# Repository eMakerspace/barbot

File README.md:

View this project on [CADLAB.io](https://cadlab.io/project/29307). 

# eMakerspace-BarBot

Design your own drinks...
- Use a WordPress configurator to design a drink
- Pay the drink with Twint
- Grab the data with a python script over the WooCommerce API
- Control the robot via the RPi HAT and make the drinks

## Web UI

## RPi HAT

## Processing an order
```
━━━━━━━┳━━━━━━━━━━━━━━━━━━━━━━━━━━━━━━━┳━━━━━━━━━━━━━━
   444 ┃ Marco                         ┃ processing
━━━━━━━╋━━━━━━━━━━━━┳━━━━━━━━━━━━━━━━━━╋━━━━━━━━━━━━━━
    ID ┃ Name       ┃ Filler           ┃ Alc
───────╂────────────╂──────────────────╂──────────────
     0 ┃ Vodka-O    ┃ Orangensaft      ┃ Vodka
     1 ┃ DIY drink  ┃ Citro            ┃ Tequila

Process order 444
Process drink  0/1: Vodka-O
Robot: Waiting for a new cup
Robot: Start movement
Robot: Pouring filler: Orangensaft
Robot: Pouring alcohol: Vodka
Robot: Completed Vodka-O
Process drink  1/1: DIY drink
Robot: Waiting for a new cup
Robot: Start movement
Robot: Pouring filler: Citro
Robot: Pouring alcohol: Tequila
Robot: Completed DIY drink
Completed order 444, upload new status to WordPress
Upload completed
```

### Limitations
No umlauts allowed in the drinks

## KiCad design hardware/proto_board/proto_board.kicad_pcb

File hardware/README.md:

# Modular Hardware

- Nothing is fixed; it will change anyway...
- Make a solid base for creative hacking
- Everything based on ribbon cable
- No free flying hardware and sketchy cables
- Every cable is keyed, no wrong polarities.

| &nbsp;                                    | &nbsp;                                          |
| ----------------------------------------- | ----------------------------------------------- |
|        |        |
|  |  |

## Underling Architecture

- Different boards e.g.
    - IO
    - DC Motors with H-Bridge
    - Stepper motors
    - Proto board
    - Raspberry Pi
    - Main ESP

## BarBot HAT

First try with a fixed version, failed at the first adaption... ;-)

- Raspberry Pi HAT
- SEED Studio ESP32-C3
- One stepper motor driver
- Five 12V outputs, with a Tiny 1.5 A MOSFET Gate Driver
- Neopixel output

| &nbsp;                              | &nbsp;                                    |
| ----------------------------------- | ----------------------------------------- |
|        |        |
|  |  |

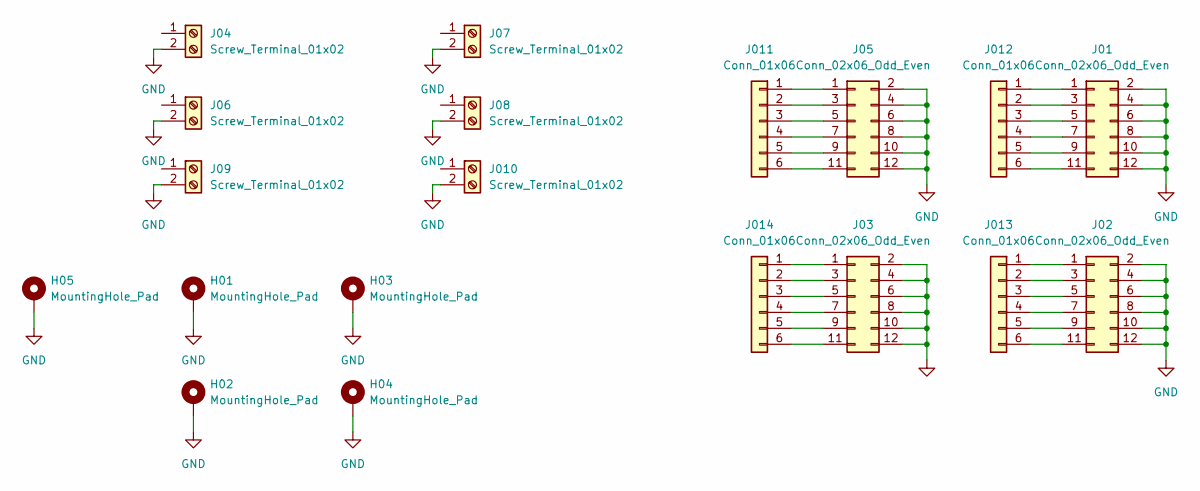
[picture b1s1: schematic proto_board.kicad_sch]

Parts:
H01, H02, H03, H04, H05: MountingHole_Pad; MountingHole_3.2mm_M3_Pad_Via
J01, J02, J03, J05: Conn_02x06_Odd_Even; PinSocket_2x06_P2.54mm_Vertical
J04, J06, J07, J08, J09, J010: Screw_Terminal_01x02; TerminalBlock_MetzConnect_Type055_RT01502HDWU_1x02_P5.00mm_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
J011, J012, J013, J014: Conn_01x06; 6Pin

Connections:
GND: H01.1 (1_1), H02.1 (1_1), H03.1 (1_1), H04.1 (1_1), H05.1 (1_1), J01.2, J01.4, J01.6, J01.8, J01.10, J01.12, J02.2, J02.4, J02.6, J02.8, J02.10, J02.12, J03.2, J03.4, J03.6, J03.8, J03.10, J03.12, J04.2 (Pin_2_2), J05.2, J05.4, J05.6, J05.8, J05.10, J05.12, J06.2 (Pin_2_2), J07.2 (Pin_2_2), J08.2 (Pin_2_2), J09.2 (Pin_2_2), J010.2 (Pin_2_2)
unnamed: J01.1, J012.1
unnamed: J01.3, J012.2
unnamed: J01.5, J012.3
unnamed: J01.7, J012.4
unnamed: J01.9, J012.5
unnamed: J01.11, J012.6
unnamed: J05.1, J011.1
unnamed: J05.3, J011.2
unnamed: J05.5, J011.3
unnamed: J05.7, J011.4
unnamed: J05.9, J011.5
unnamed: J05.11, J011.6
unnamed: J02.1, J013.1
unnamed: J02.3, J013.2
unnamed: J02.5, J013.3
unnamed: J02.7, J013.4
unnamed: J02.9, J013.5
unnamed: J02.11, J013.6
unnamed: J03.1, J014.1
unnamed: J03.3, J014.2
unnamed: J03.5, J014.3
unnamed: J03.7, J014.4
unnamed: J03.9, J014.5
unnamed: J03.11, J014.6

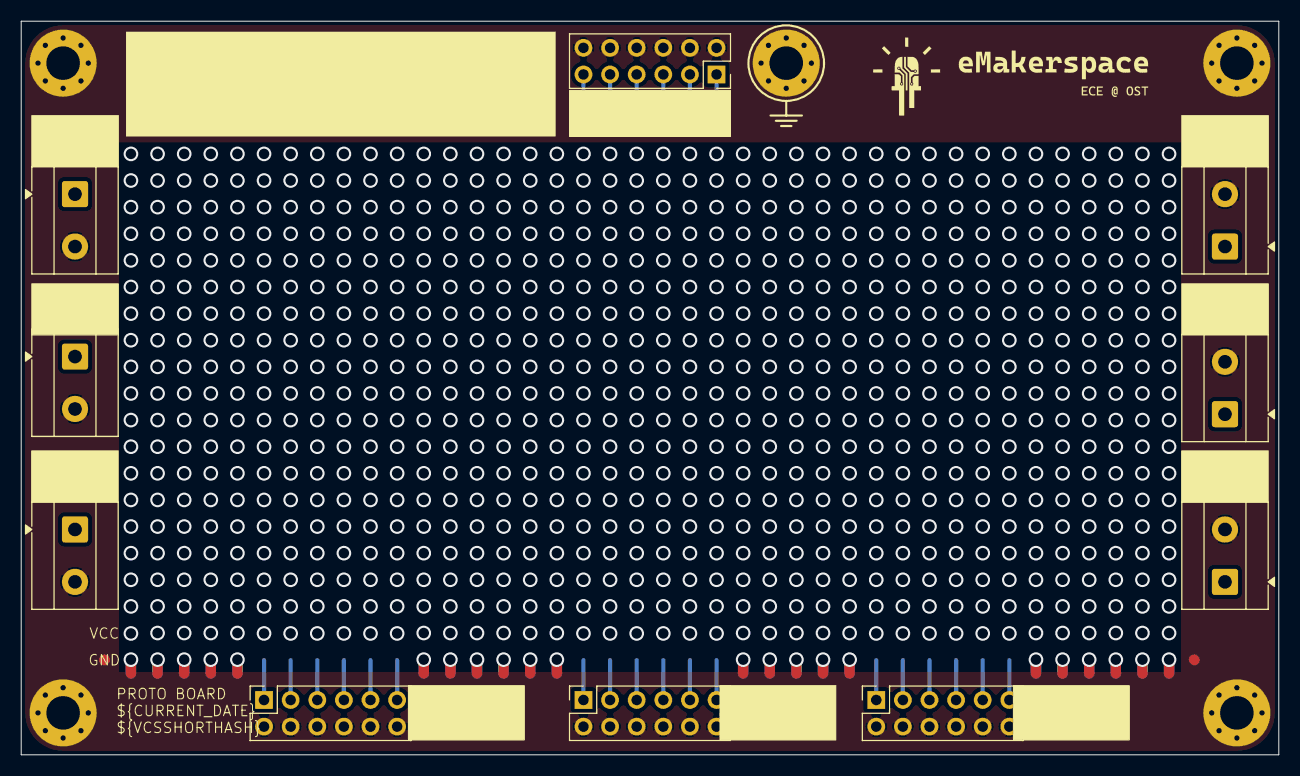
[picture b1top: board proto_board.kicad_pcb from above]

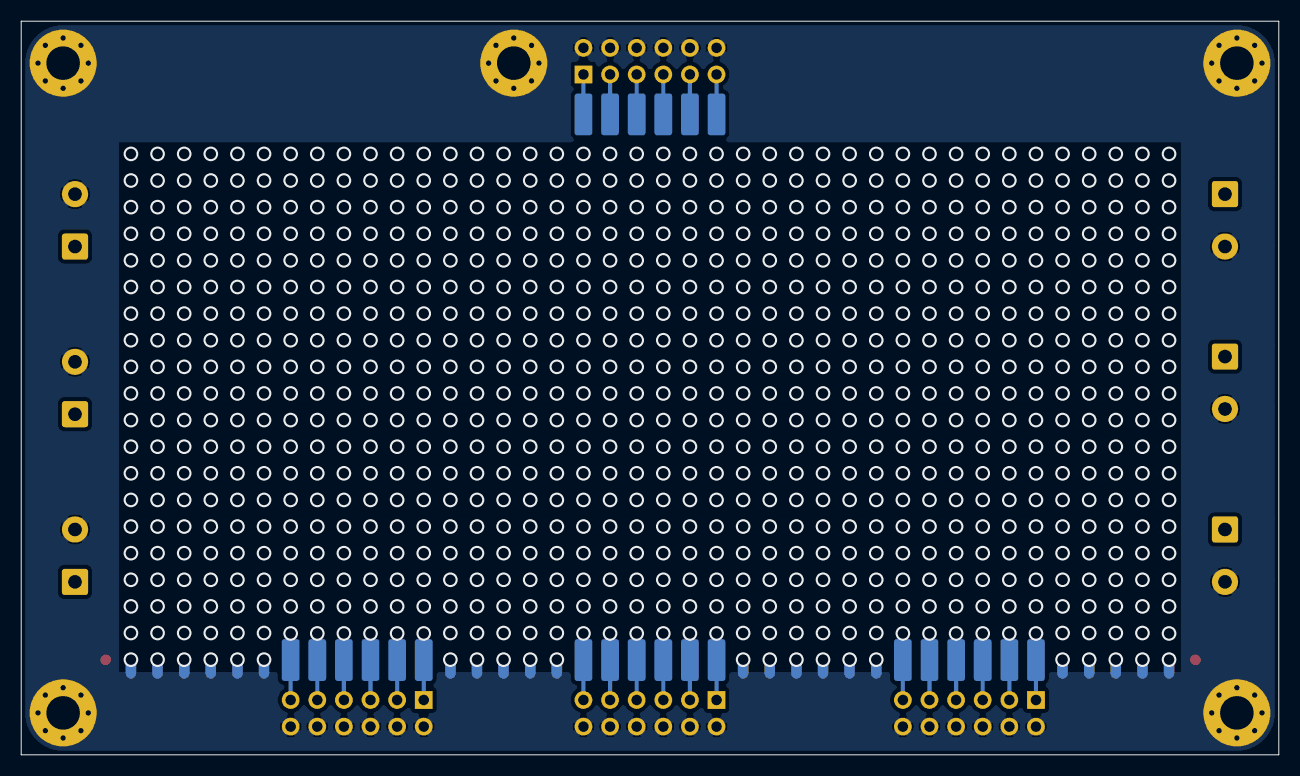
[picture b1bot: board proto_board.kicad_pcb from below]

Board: 2 copper layers, 120.0 x 70.0 mm, 19 parts (4 on the bottom side), 25 nets.

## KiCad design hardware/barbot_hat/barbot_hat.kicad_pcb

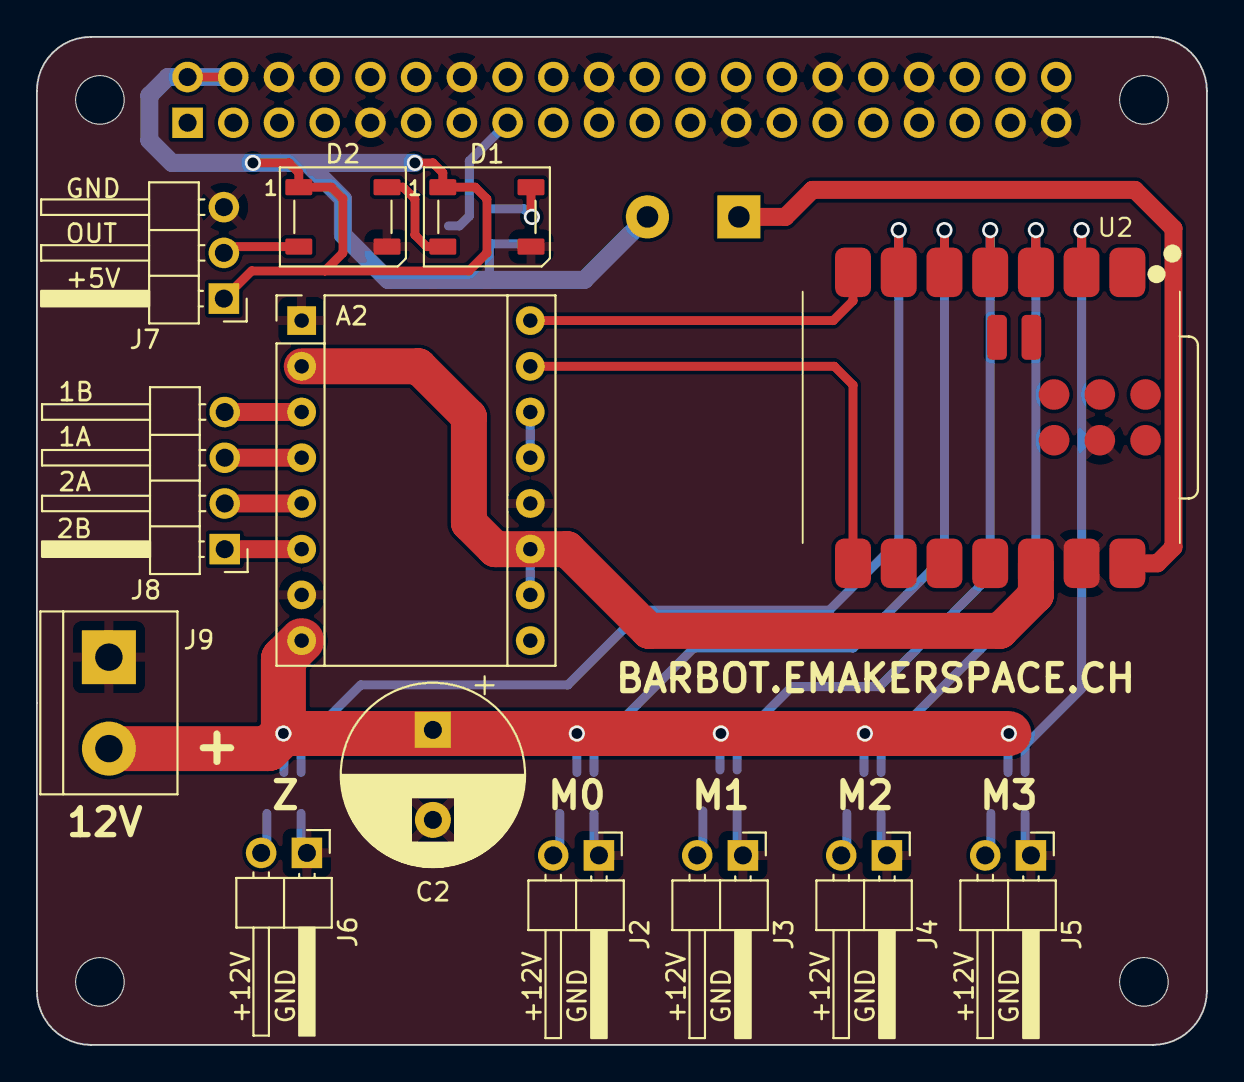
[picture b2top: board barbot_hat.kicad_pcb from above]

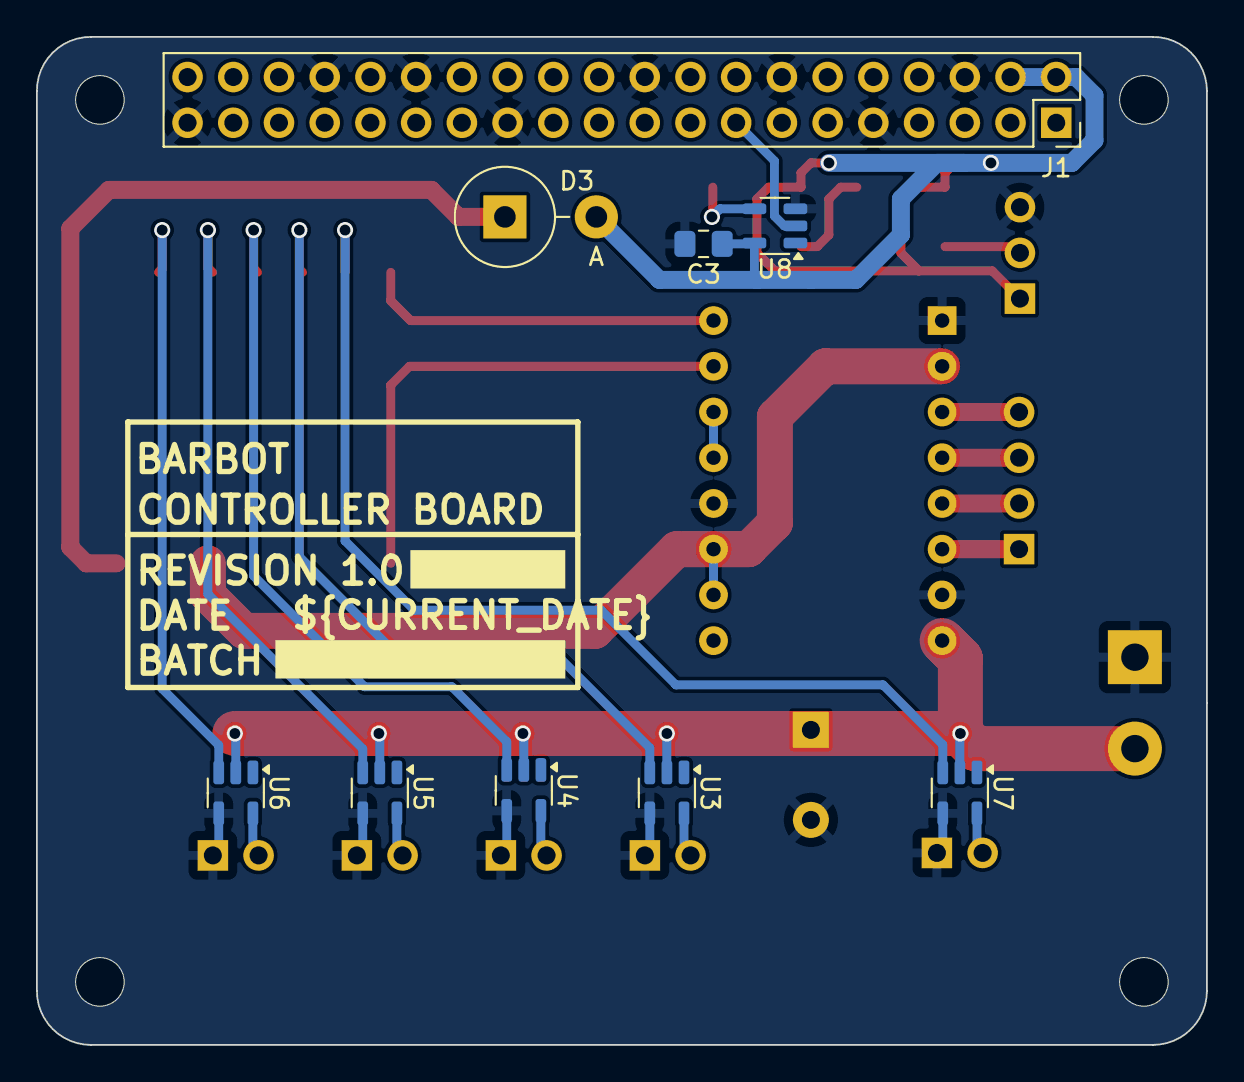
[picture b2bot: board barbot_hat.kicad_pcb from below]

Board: 2 copper layers, 65.0 x 56.0 mm, 26 parts (9 on the bottom side), 26 nets.

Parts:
A2: Pololu_Breakout_A4988; Pololu_Breakout-16_15.2x20.3mm
C2: C_Polarized; CP_Radial_D10.0mm_P5.00mm
C3: C; C_0805_2012Metric_Pad1.18x1.45mm_HandSolder
D1, D2: WS2812B; LED_WS2812B_PLCC4_5.0x5.0mm_P3.2mm
D3: D; D_DO-27_P5.08mm_Vertical_AnodeUp
J1: GPIO; PinSocket_2x20_P2.54mm_Vertical
J2, J3, J4, J5, J6: Conn_01x02; PinHeader_1x02_P2.54mm_Horizontal
J7: Conn_01x03; PinHeader_1x03_P2.54mm_Horizontal
J8: Conn_01x04; PinHeader_1x04_P2.54mm_Horizontal
J9: Screw_Terminal_01x02; TerminalBlock_bornier-2_P5.08mm
MH1, MH2, MH3, MH4: MountingHole_2.7mm_M2.5
U2: XIAO-ESP32C3-SMD
U3, U4, U5, U6, U7: MCP1416; SOT-23-5
U8: SN74LV1T34DBV; SOT-23-5

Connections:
+3V3: A2.2 (VDD), A2.10 (MS1), A2.11 (MS2), U2.12 (3V3)
+5V: C3.1, D1.1 (VDD), D2.1 (VDD), D3.2 (A), J1.2, J1.4, J7.1, U8.5 (VCC)
+12V: A2.8 (VMOT), C2.1, J9.2, U3.2 (Vdd), U4.2 (Vdd), U5.2 (Vdd), U6.2 (Vdd), U7.2 (Vdd)
/1A: A2.4 (1A), J8.3
/1B: A2.3 (1B), J8.4
/2A: A2.5 (2A), J8.2
/2B: A2.6 (2B), J8.1
/GPIO22 / NEOPIXEL_IN: J1.15, U8.2 (A)
/MOTOR_X_DIR: A2.16 (DIR), U2.7 (GPIO21)
/MOTOR_X_STEP: A2.15 (STEP), U2.8 (GPIO20)
/MOTOR_Z: U2.6 (GPIO7), U7.3 (IN)
/NEOPIXEL_OUT: D2.2 (DOUT), J7.2
/PUMP_CTRL0: U2.5 (GPIO6), U3.3 (IN)
/PUMP_CTRL1: U2.4 (GPIO5), U4.3 (IN)
/PUMP_CTRL2: U2.3 (GPIO4), U5.3 (IN)
/PUMP_CTRL3: U2.2 (GPIO3), U6.3 (IN)
GND: A2.1 (GND), A2.7 (GND), A2.12 (MS3), C2.2, C3.2, D1.3 (VSS), D2.3 (VSS), J1.6, J1.9, J1.14, J1.20, J1.25, J1.30, J1.34, J1.39, J2.1, J3.1, J4.1, J5.1, J6.1, J7.3, J9.1, U2.13 (GND), U2.20 (GND), U3.4 (GND), U4.4 (GND), U5.4 (GND), U6.4 (GND), U7.4 (GND), U8.3 (GND)
unnamed: A2.13 (~RESET), A2.14 (~SLEEP)
unnamed: D1.4 (DIN), U8.4 (Y)
unnamed: D1.2 (DOUT), D2.4 (DIN)
unnamed: D3.1 (K), U2.14 (5V)
unnamed: J2.2, U3.5 (OUT)
unnamed: J3.2, U4.5 (OUT)
unnamed: J4.2, U5.5 (OUT)
unnamed: J5.2, U6.5 (OUT)
unnamed: J6.2, U7.5 (OUT)

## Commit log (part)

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2024-01-03 Work on modules
2024-01-03 Add readme.md
2024-01-07 Improve code, add error handling
2024-01-10 Update to new website
2024-11-08 Rework api and roboter interface
2024-11-09 Move bottle storage into a database
2024-11-11 Add original arduino file
    this is unfortunately the old version which does not have a smooth
    acceleration of the servo motor. The improved version is gone.
    Only use it as a reference and do not upload it to the ESP32 mounted on the barbot!
    For testing, use a different ESP32 board and clip it to the barbot.
2024-12-16 Add code for serial communication
2024-12-16 Add readme for python code
2024-12-17 Remove wait for idle
2024-12-17 Uodate readme, cleanup example file
2024-12-18 Create LICENSE
2024-12-18 Rename license file
2024-12-18 Add ring control + homing
2024-12-18 renamed variables
    used "Sound" instead of pressing motor, because otherwise chatgpt always set Z as coordinate and not time.
    Rename variables for correctness
2024-12-18 Dummy statemachine created
    working state machine using common gcode notation. Sample code:
    X for position (1-12), Z for pressing duration (in ms)
    sample code:
    G1 X11 Z2500
    G28
    G1 X12 Z2000
2024-12-18 Working script
    Allowed commands:
    G1 X4 Z4000 // goto pos4, press 4000ms
    G1 Z2000 // press 4000ms
    G28 // home
    M0 // STOP (while 1)
    STATUS // returns idle or busy
2024-12-18 Add README.md for ESP32
2024-12-20 Add retraction before Homing, and other fixes
2024-12-20 Remove test files
    # Conflicts:
    # esp32/serial_test/serial_test.ino
    # esp32/stepper_test/stepper_test.ino
2025-04-18 Start with PCB design
2025-04-22 Work on layout
2025-04-22 Add stepper ref image to schematic
2025-04-23 Change power delivery, update logo
2025-04-23 Update front silk
2025-04-24 Update images and readme
2025-04-25 Backlink to CADLAB.io has been added.
2025-05-01 Add initial esp32 firmware setup
2025-05-03 Add gcode parsing, begin stepper control
2025-05-08 Implement stepper motor control
2025-05-08 Fix typo
2025-05-20 Improve stepper, implement gcode commands
    Add crate `stepgen` as local module (copy-paste), to make changes in the
    future.
2025-05-20 Fix warnings
2025-09-10 Update pump motor
2025-12-14 Update dependencies, pin assignments
2025-12-14 Refactor, implement homing
2025-12-15 Docs
2025-12-16 Upgrade to 2024 edition, refactor RMT driver
2025-12-16 Implement recovering from emergency stop
2025-12-16 Implement pump control, wait until emergency is cleared
2025-12-18 Lift motor, fixes, more commands
2025-12-18 Implement fractional range position
2025-12-18 Small fixes
2025-12-18 Some comments
2025-12-18 Fix emergency stop release logic
2026-03-31 add new implementation for raspi
2026-04-06 update python script v2
2026-04-06 implement LCD display in python script v2
2026-04-09 add HAL
2026-04-09 add custom PHP snippets for wordpress (for documentation)
2026-04-09 clean up
2026-04-09 order processing mockup
2026-04-09 Implement order progress tracking and update LCD menu for drink mixing
2026-04-11 added heartbeat thread for the homepage
2026-04-11 remove temp files
2026-04-13 added 7 segment and neopixel source code
2026-04-23 rework python script
2026-04-23 add esp32 pump logic
2026-04-23 Add config
2026-04-23 Add firmware
2026-04-23 push
2026-04-23 ES TUETgit statusgit status FIRST STABLE
2026-04-26 remove legacy code
2026-04-26 removed simulation
2026-04-26 removed emergency stop
2026-04-26 remove more simulation
2026-04-26 fix retry and remove that only mixers are retried and the entire drink will be made new
2026-04-26 remove pin lock
2026-04-26 remove unused functions/imports
2026-04-26 save pause before moving servo
2026-04-27 fix issue 1-3
2026-04-27 add debug docs
2026-04-27 fix led position and slow down homing
2026-04-27 remove _broadcast
2026-04-27 homing timeout to 240s
2026-04-27 logger use time instead of elapsed
2026-04-27 increase homing timeout again
2026-04-28 if cup is already present, do not wait and begin with countdown
2026-04-28 add reverse and fix retry
2026-04-28 add retract start
2026-04-28 forward declarations
2026-04-28 fix retry
2026-04-28 update neopixel animations
2026-04-28 resolve exception
2026-04-28 update animations
2026-04-28 fix lcd
2026-04-28 replace cup if failed
2026-04-28 replace cup if failed 2
2026-04-29 set retract to 1 second
2026-05-01 increase pouring tolerance
2026-05-01 timeout increased to 60s
2026-05-01 set pour timeout to 60 on python
2026-05-01 Changes in weight logging to see if esp works
2026-05-01 Add a simple standalone script to show IP address on screen.
2026-05-01 update ip read script
2026-05-01 do not turn off backlight
2026-05-05 Add draft for modular architecture and proto board
2026-05-05 Add documentation for new architecture
2026-05-05 Add solder pads to ribbon cable
2026-05-05 Fix schematic
